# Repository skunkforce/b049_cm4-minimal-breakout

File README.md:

# edgy_board number b078
This design is part of the [edgy board project](https://github.com/skunkforce/edgy_boards).

# getting started
This repository uses submodules. After cloning use the command 

```$ git submodule update --init --recursive```

to pull the submodules before opening the project with kicad. 

# Tests
Tests can be found in TESTS.md

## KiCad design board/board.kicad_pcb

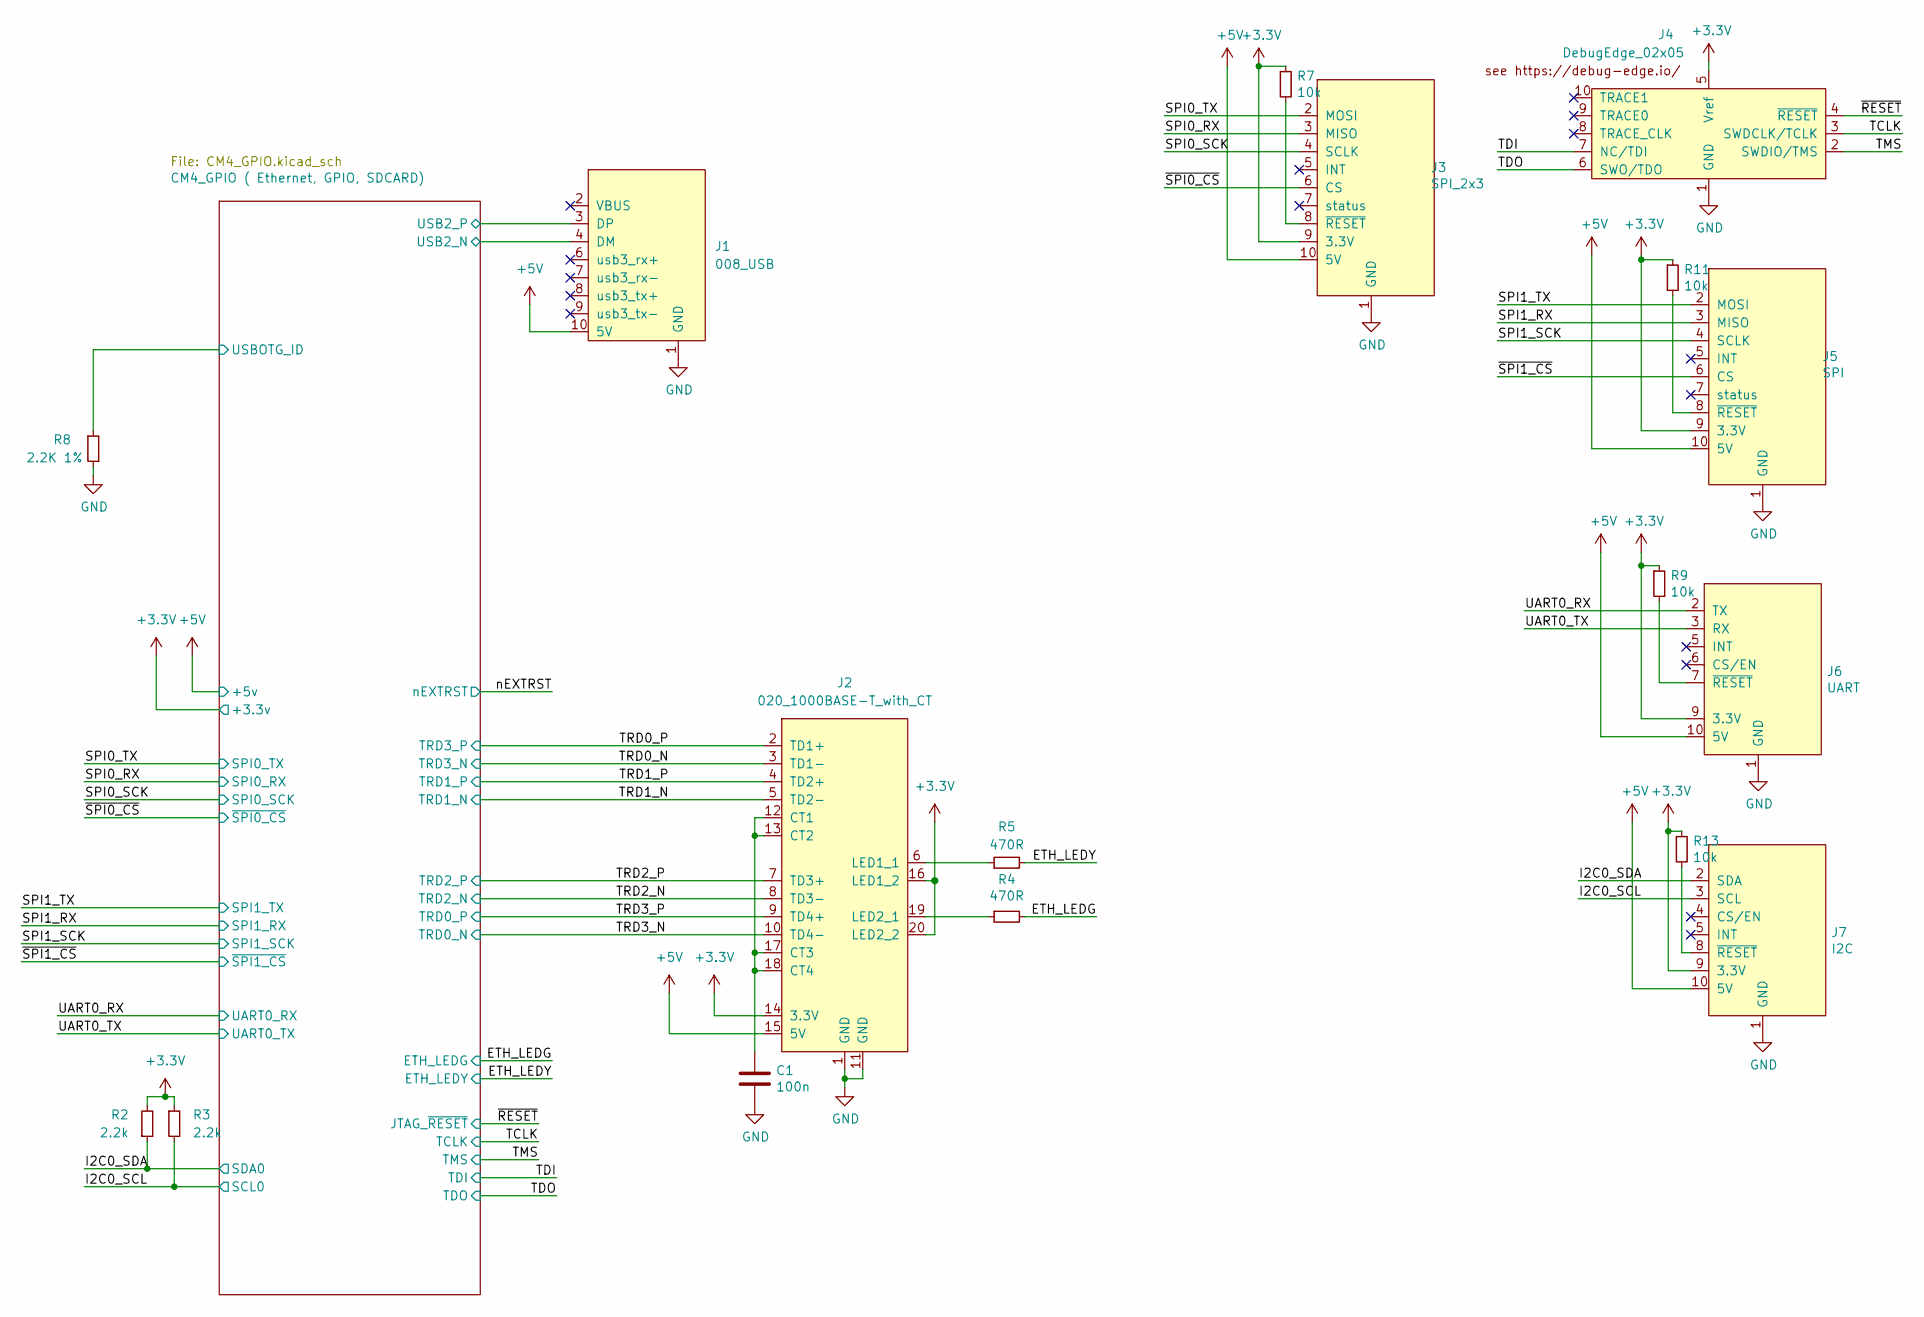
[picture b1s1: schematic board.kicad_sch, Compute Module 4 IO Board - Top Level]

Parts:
C1: 100n; C_0402_1005Metric; Part Description 0.1uF 10% 16V Ceramic Capacitor X7R 040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
J1: 008_USB; on_edge_2x05_host
J2: 020_1000BASE-T_with_CT; on_edge_2x10_host
J3: SPI_2x3; on_edge_2x05_up_host
J4: DebugEdge_02x05; debug_edge_2x05_host
J5: SPI; on_edge_2x05_host
J6: UART; on_edge_2x05_host
J7: I2C; on_edge_2x05_host
R2, R3: 2.2k; R_0603_1608Metric
R4, R5: 470R; R_0402_1005Metric; Part Description Resistor 470R M1005 1% 63mW
R7, R9, R11, R13: 10k; R_0603_1608Metric
R8: 2.2K 1%; R_0402_1005Metric; Part Description Resistor 2.2K M1005 1% 63mW

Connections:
+3.3V: J2.14 (3.3V), J2.16 (LED1_2), J2.20 (LED2_2), J3.9 (3.3V), J4.5 (Vref), J5.9 (3.3V), J6.9 (3.3V), J7.9 (3.3V), R2.2, R3.1, R7.1, R9.1, R11.1, R13.1; also elsewhere on the board
+5V: J1.10 (5V), J2.15 (5V), J3.10 (5V), J5.10 (5V), J6.10 (5V), J7.10 (5V); also elsewhere on the board
/CM4_GPIO ( Ethernet, GPIO, SDCARD)/USB2_N: J1.4 (DM); also elsewhere on the board
/CM4_GPIO ( Ethernet, GPIO, SDCARD)/USB2_P: J1.3 (DP); also elsewhere on the board
/CM4_GPIO ( Ethernet, GPIO, SDCARD)/USBOTG_ID: R8.1; also elsewhere on the board
/ETH_LEDG: R4.2; also elsewhere on the board
/ETH_LEDY: R5.2; also elsewhere on the board
/I2C0_SCL: J7.3 (SCL), R3.2; also elsewhere on the board
/I2C0_SDA: J7.2 (SDA), R2.1; also elsewhere on the board
/SPI0_RX: J3.3 (MISO); also elsewhere on the board
/SPI0_SCK: J3.4 (SCLK); also elsewhere on the board
/SPI0_TX: J3.2 (MOSI); also elsewhere on the board
/SPI1_RX: J5.3 (MISO); also elsewhere on the board
/SPI1_SCK: J5.4 (SCLK); also elsewhere on the board
/SPI1_TX: J5.2 (MOSI); also elsewhere on the board
/TCLK: J4.3 (SWDCLK/TCLK); also elsewhere on the board
/TDI: J4.7 (NC/TDI); also elsewhere on the board
/TDO: J4.6 (SWO/TDO); also elsewhere on the board
/TMS: J4.2 (SWDIO/TMS); also elsewhere on the board
/TRD0_N: J2.3 (TD1-); also elsewhere on the board
/TRD0_P: J2.2 (TD1+); also elsewhere on the board
/TRD1_N: J2.5 (TD2-); also elsewhere on the board
/TRD1_P: J2.4 (TD2+); also elsewhere on the board
/TRD2_N: J2.8 (TD3-); also elsewhere on the board
/TRD2_P: J2.7 (TD3+); also elsewhere on the board
/TRD3_N: J2.10 (TD4-); also elsewhere on the board
/TRD3_P: J2.9 (TD4+); also elsewhere on the board
/UART0_RX: J6.2 (TX); also elsewhere on the board
/UART0_TX: J6.3 (RX); also elsewhere on the board
/~RESET: J4.4 (~RESET); also elsewhere on the board
/~SPI0_CS: J3.6 (CS); also elsewhere on the board
/~SPI1_CS: J5.6 (CS); also elsewhere on the board
GND: C1.2, J1.1 (GND), J2.1 (GND), J2.11 (GND), J3.1 (GND), J4.1 (GND), J5.1 (GND), J6.1 (GND), J7.1 (GND), R8.2; also elsewhere on the board
unnamed: C1.1, J2.12 (CT1), J2.13 (CT2), J2.17 (CT3), J2.18 (CT4)
unnamed: J2.6 (LED1_1), R5.1
unnamed: J2.19 (LED2_1), R4.1
unnamed: J3.8 (~RESET), R7.2
unnamed: J5.8 (~RESET), R11.2
unnamed: J6.7 (~RESET), R9.2
unnamed: J7.8 (~RESET), R13.2

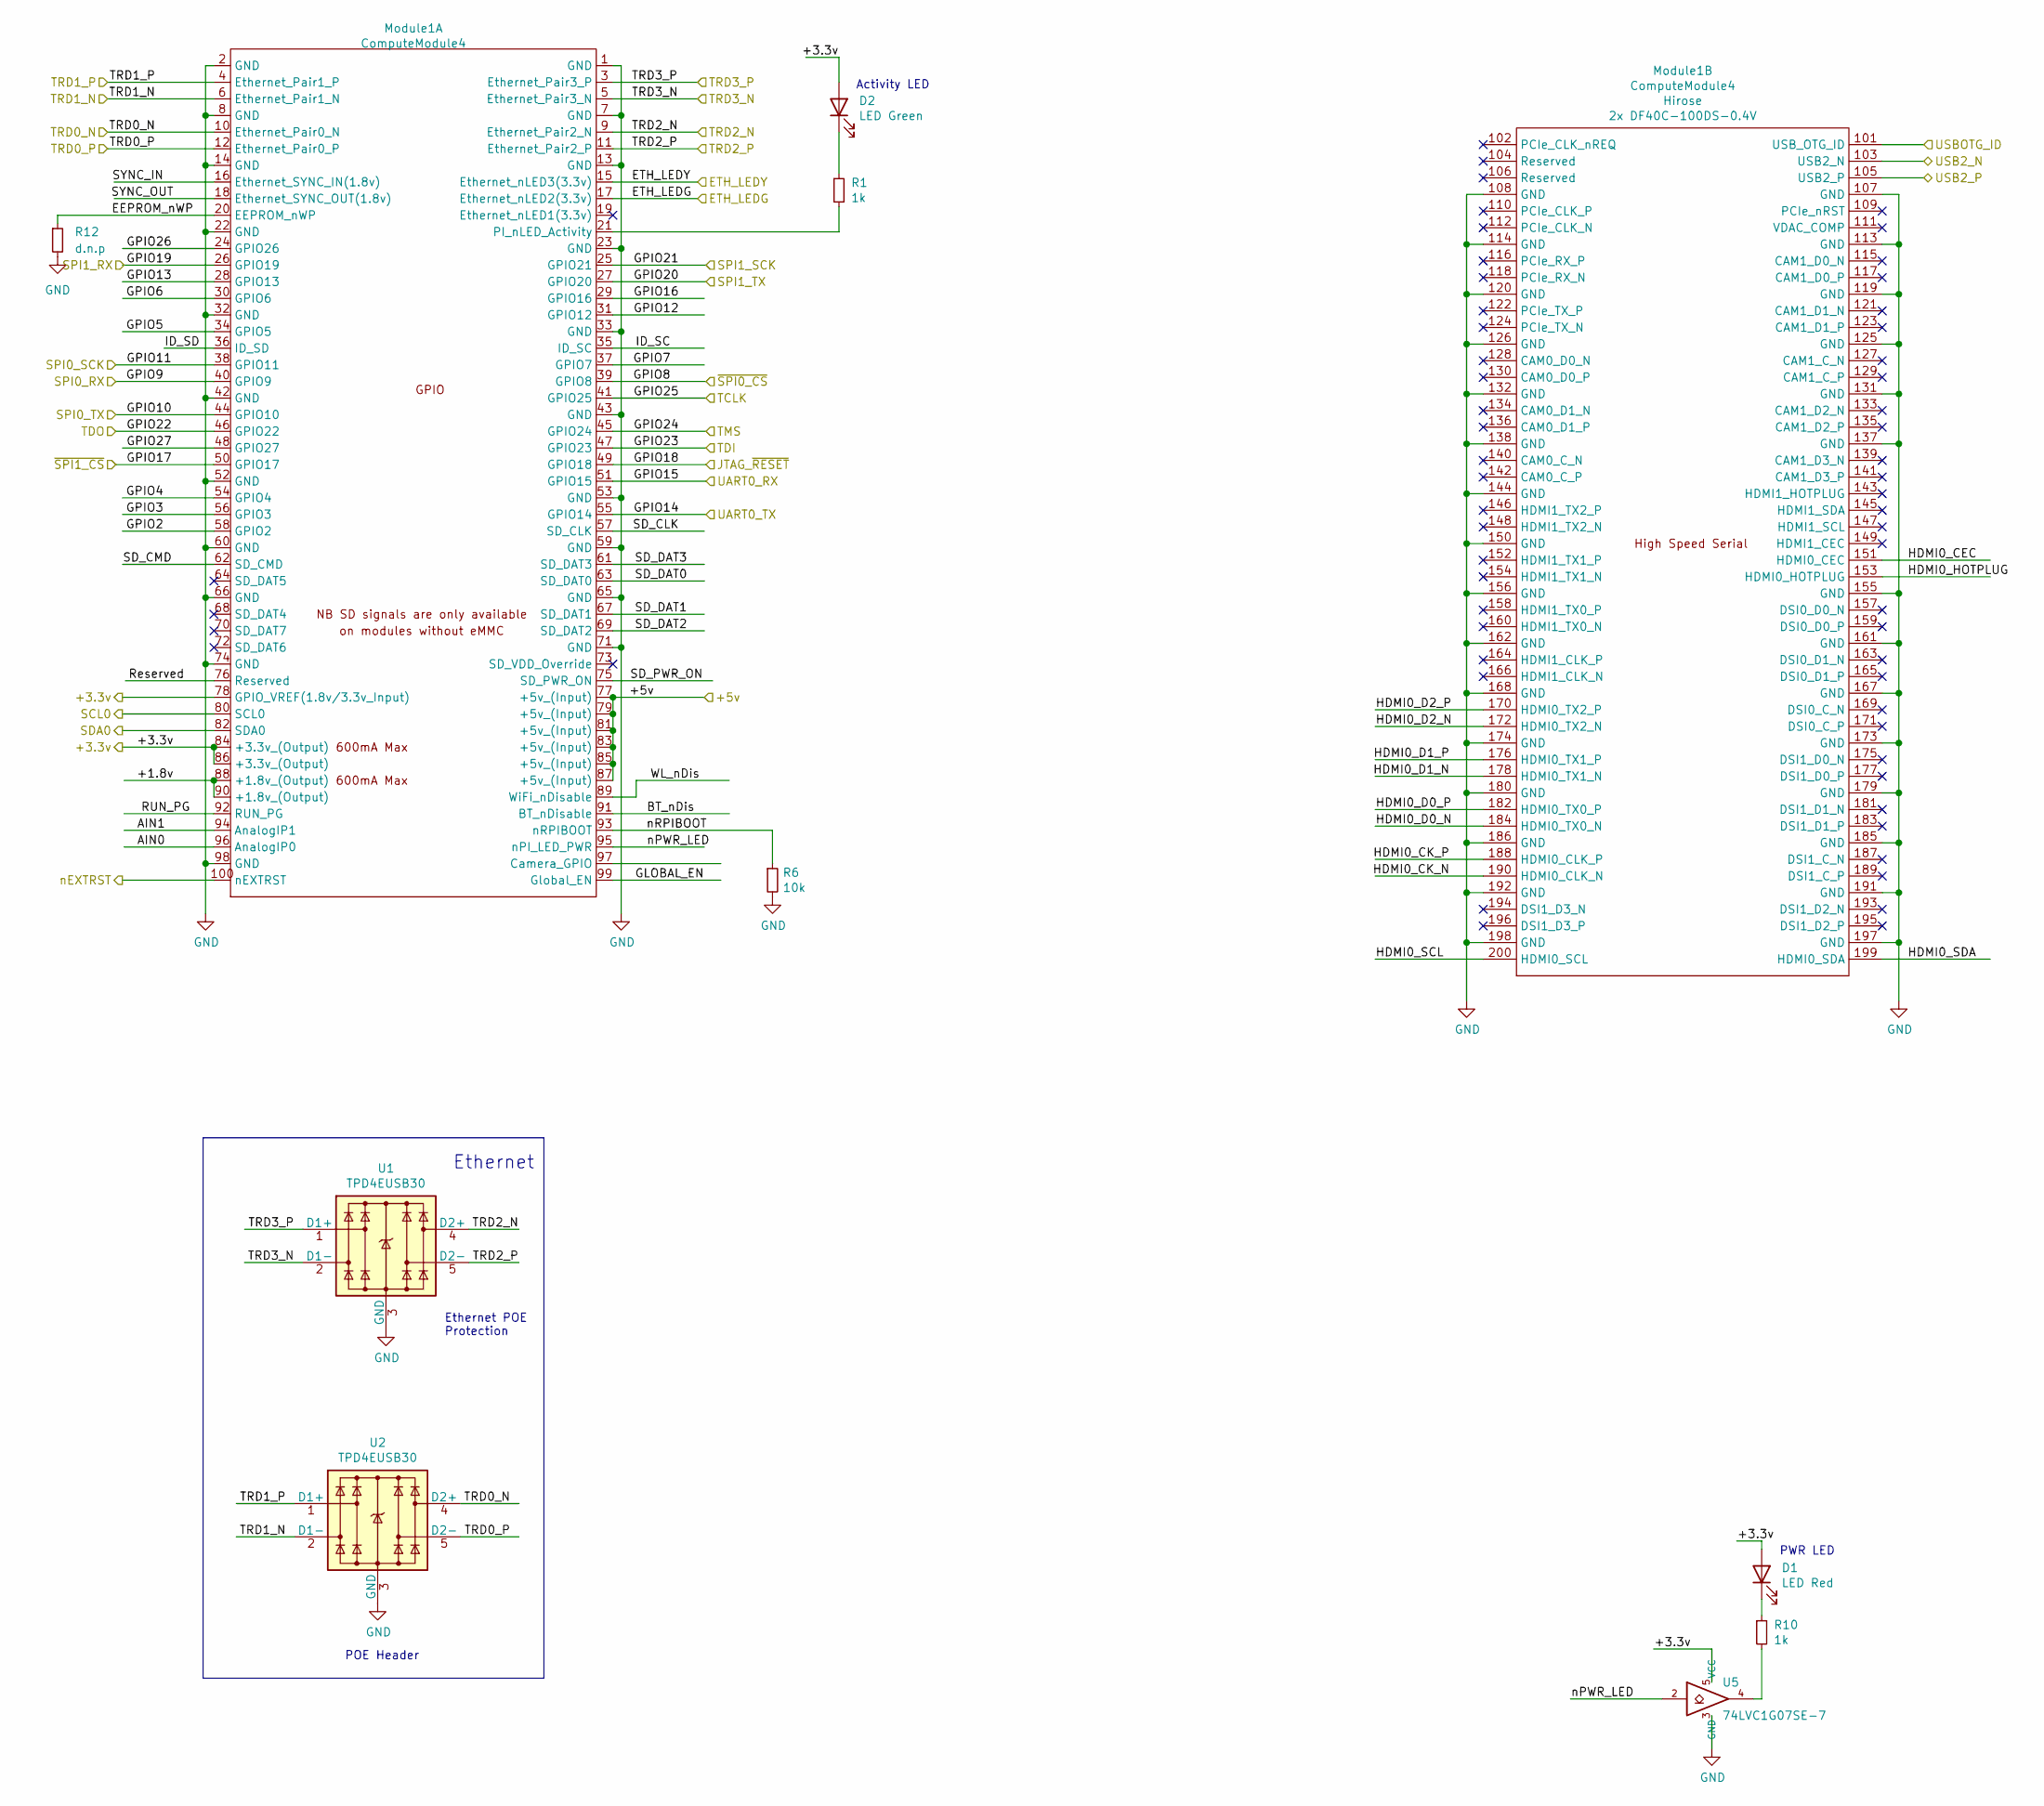
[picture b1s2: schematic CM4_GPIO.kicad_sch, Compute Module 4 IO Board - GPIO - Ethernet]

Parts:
D1: LED Red; LED_0603_1608Metric; Part Description Red 620nm LED Indication - Discrete 2.2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
D2: LED Green; LED_0603_1608Metric; Part Description Green 572nm LED Indication - Discrete 2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
Module1: ComputeModule4; Raspberry-Pi-4-Compute-Module; Part Description 100 Position Connector Receptacle, Cent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
R1, R10: 1k; R_0402_1005Metric; Part Description Resistor 1K M1005 1% 63mW
R6: 10k; R_0603_1608Metric
R12: d.n.p; R_0603_1608Metric
U1, U2: TPD4EUSB30; USON-10_2.5x1.0mm_P0.5mm; Part Description Quad TVS diode for high speed signals (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
U5: 74LVC1G07SE-7; SOT-353_SC-70-5; Part Description Buffer, Non-Inverting 1 Element 1 Bit p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

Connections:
+3.3V: D1.2 (A), D2.2 (A), Module1.78 (GPIO_VREF(1.8v/3.3v_Input)), Module1.84 (+3.3v_(Output)), Module1.86 (+3.3v_(Output)), U5.5 (VCC); also elsewhere on the board
+5V: Module1.77 (+5v_(Input)), Module1.79 (+5v_(Input)), Module1.81 (+5v_(Input)), Module1.83 (+5v_(Input)), Module1.85 (+5v_(Input)), Module1.87 (+5v_(Input)); also elsewhere on the board
/CM4_GPIO ( Ethernet, GPIO, SDCARD)/+1.8v: Module1.88 (+1.8v_(Output)), Module1.90 (+1.8v_(Output))
/CM4_GPIO ( Ethernet, GPIO, SDCARD)/AIN0: Module1.96 (AnalogIP0)
/CM4_GPIO ( Ethernet, GPIO, SDCARD)/AIN1: Module1.94 (AnalogIP1)
/CM4_GPIO ( Ethernet, GPIO, SDCARD)/BT_nDis: Module1.91 (BT_nDisable)
/CM4_GPIO ( Ethernet, GPIO, SDCARD)/EEPROM_nWP: Module1.20 (EEPROM_nWP), R12.1
/CM4_GPIO ( Ethernet, GPIO, SDCARD)/GLOBAL_EN: Module1.99 (Global_EN)
/CM4_GPIO ( Ethernet, GPIO, SDCARD)/GPIO2: Module1.58 (GPIO2)
/CM4_GPIO ( Ethernet, GPIO, SDCARD)/GPIO3: Module1.56 (GPIO3)
/CM4_GPIO ( Ethernet, GPIO, SDCARD)/GPIO4: Module1.54 (GPIO4)
/CM4_GPIO ( Ethernet, GPIO, SDCARD)/GPIO5: Module1.34 (GPIO5)
/CM4_GPIO ( Ethernet, GPIO, SDCARD)/GPIO6: Module1.30 (GPIO6)
/CM4_GPIO ( Ethernet, GPIO, SDCARD)/GPIO7: Module1.37 (GPIO7)
/CM4_GPIO ( Ethernet, GPIO, SDCARD)/GPIO12: Module1.31 (GPIO12)
/CM4_GPIO ( Ethernet, GPIO, SDCARD)/GPIO13: Module1.28 (GPIO13)
/CM4_GPIO ( Ethernet, GPIO, SDCARD)/GPIO16: Module1.29 (GPIO16)
/CM4_GPIO ( Ethernet, GPIO, SDCARD)/GPIO26: Module1.24 (GPIO26)
/CM4_GPIO ( Ethernet, GPIO, SDCARD)/GPIO27: Module1.48 (GPIO27)
/CM4_GPIO ( Ethernet, GPIO, SDCARD)/HDMI0_CEC: Module1.151 (HDMI0_CEC)
/CM4_GPIO ( Ethernet, GPIO, SDCARD)/HDMI0_CK_N: Module1.190 (HDMI0_CLK_N)
/CM4_GPIO ( Ethernet, GPIO, SDCARD)/HDMI0_CK_P: Module1.188 (HDMI0_CLK_P)
/CM4_GPIO ( Ethernet, GPIO, SDCARD)/HDMI0_D0_N: Module1.184 (HDMI0_TX0_N)
/CM4_GPIO ( Ethernet, GPIO, SDCARD)/HDMI0_D0_P: Module1.182 (HDMI0_TX0_P)
/CM4_GPIO ( Ethernet, GPIO, SDCARD)/HDMI0_D1_N: Module1.178 (HDMI0_TX1_N)
/CM4_GPIO ( Ethernet, GPIO, SDCARD)/HDMI0_D1_P: Module1.176 (HDMI0_TX1_P)
/CM4_GPIO ( Ethernet, GPIO, SDCARD)/HDMI0_D2_N: Module1.172 (HDMI0_TX2_N)
/CM4_GPIO ( Ethernet, GPIO, SDCARD)/HDMI0_D2_P: Module1.170 (HDMI0_TX2_P)
/CM4_GPIO ( Ethernet, GPIO, SDCARD)/HDMI0_HOTPLUG: Module1.153 (HDMI0_HOTPLUG)
/CM4_GPIO ( Ethernet, GPIO, SDCARD)/HDMI0_SCL: Module1.200 (HDMI0_SCL)
/CM4_GPIO ( Ethernet, GPIO, SDCARD)/HDMI0_SDA: Module1.199 (HDMI0_SDA)
/CM4_GPIO ( Ethernet, GPIO, SDCARD)/ID_SC: Module1.35 (ID_SC)
/CM4_GPIO ( Ethernet, GPIO, SDCARD)/ID_SD: Module1.36 (ID_SD)
/CM4_GPIO ( Ethernet, GPIO, SDCARD)/RUN_PG: Module1.92 (RUN_PG)
/CM4_GPIO ( Ethernet, GPIO, SDCARD)/Reserved: Module1.76 (Reserved)
/CM4_GPIO ( Ethernet, GPIO, SDCARD)/SD_CLK: Module1.57 (SD_CLK)
/CM4_GPIO ( Ethernet, GPIO, SDCARD)/SD_CMD: Module1.62 (SD_CMD)
/CM4_GPIO ( Ethernet, GPIO, SDCARD)/SD_DAT0: Module1.63 (SD_DAT0)
/CM4_GPIO ( Ethernet, GPIO, SDCARD)/SD_DAT1: Module1.67 (SD_DAT1)
/CM4_GPIO ( Ethernet, GPIO, SDCARD)/SD_DAT2: Module1.69 (SD_DAT2)
/CM4_GPIO ( Ethernet, GPIO, SDCARD)/SD_DAT3: Module1.61 (SD_DAT3)
/CM4_GPIO ( Ethernet, GPIO, SDCARD)/SD_PWR_ON: Module1.75 (SD_PWR_ON)
/CM4_GPIO ( Ethernet, GPIO, SDCARD)/SYNC_IN: Module1.16 (Ethernet_SYNC_IN(1.8v))
/CM4_GPIO ( Ethernet, GPIO, SDCARD)/SYNC_OUT: Module1.18 (Ethernet_SYNC_OUT(1.8v))
/CM4_GPIO ( Ethernet, GPIO, SDCARD)/USB2_N: Module1.103 (USB2_N); also elsewhere on the board
/CM4_GPIO ( Ethernet, GPIO, SDCARD)/USB2_P: Module1.105 (USB2_P); also elsewhere on the board
/CM4_GPIO ( Ethernet, GPIO, SDCARD)/USBOTG_ID: Module1.101 (USB_OTG_ID); also elsewhere on the board
/CM4_GPIO ( Ethernet, GPIO, SDCARD)/WL_nDis: Module1.89 (WiFi_nDisable)
/CM4_GPIO ( Ethernet, GPIO, SDCARD)/nPWR_LED: Module1.95 (nPI_LED_PWR), U5.2
/CM4_GPIO ( Ethernet, GPIO, SDCARD)/nRPIBOOT: Module1.93 (nRPIBOOT), R6.1
/ETH_LEDG: Module1.17 (Ethernet_nLED2(3.3v)); also elsewhere on the board
/ETH_LEDY: Module1.15 (Ethernet_nLED3(3.3v)); also elsewhere on the board
/I2C0_SCL: Module1.80 (SCL0); also elsewhere on the board
/I2C0_SDA: Module1.82 (SDA0); also elsewhere on the board
/SPI0_RX: Module1.40 (GPIO9); also elsewhere on the board
/SPI0_SCK: Module1.38 (GPIO11); also elsewhere on the board
/SPI0_TX: Module1.44 (GPIO10); also elsewhere on the board
/SPI1_RX: Module1.26 (GPIO19); also elsewhere on the board
/SPI1_SCK: Module1.25 (GPIO21); also elsewhere on the board
/SPI1_TX: Module1.27 (GPIO20); also elsewhere on the board
/TCLK: Module1.41 (GPIO25); also elsewhere on the board
/TDI: Module1.47 (GPIO23); also elsewhere on the board
/TDO: Module1.46 (GPIO22); also elsewhere on the board
/TMS: Module1.45 (GPIO24); also elsewhere on the board
/TRD0_N: Module1.5 (Ethernet_Pair3_N), U1.2 (D1-), U1.9; also elsewhere on the board
/TRD0_P: Module1.3 (Ethernet_Pair3_P), U1.1 (D1+), U1.10; also elsewhere on the board
/TRD1_N: Module1.6 (Ethernet_Pair1_N), U2.2 (D1-), U2.9; also elsewhere on the board
/TRD1_P: Module1.4 (Ethernet_Pair1_P), U2.1 (D1+), U2.10; also elsewhere on the board
/TRD2_N: Module1.9 (Ethernet_Pair2_N), U1.4 (D2+), U1.7; also elsewhere on the board
/TRD2_P: Module1.11 (Ethernet_Pair2_P), U1.5 (D2-), U1.6; also elsewhere on the board
/TRD3_N: Module1.10 (Ethernet_Pair0_N), U2.4 (D2+), U2.7; also elsewhere on the board
/TRD3_P: Module1.12 (Ethernet_Pair0_P), U2.5 (D2-), U2.6; also elsewhere on the board
/UART0_RX: Module1.51 (GPIO15); also elsewhere on the board
/UART0_TX: Module1.55 (GPIO14); also elsewhere on the board
/nEXTRST: Module1.100 (nEXTRST)
/~RESET: Module1.49 (GPIO18); also elsewhere on the board
/~SPI0_CS: Module1.39 (GPIO8); also elsewhere on the board
/~SPI1_CS: Module1.50 (GPIO17); also elsewhere on the board
GND: Module1.1 (GND), Module1.2 (GND), Module1.7 (GND), Module1.8 (GND), Module1.13 (GND), Module1.14 (GND), Module1.22 (GND), Module1.23 (GND), Module1.32 (GND), Module1.33 (GND), Module1.42 (GND), Module1.43 (GND), Module1.52 (GND), Module1.53 (GND), Module1.59 (GND), Module1.60 (GND), Module1.65 (GND), Module1.66 (GND), Module1.71 (GND), Module1.74 (GND), Module1.98 (GND), Module1.107 (GND), Module1.108 (GND), Module1.113 (GND), Module1.114 (GND), Module1.119 (GND), Module1.120 (GND), Module1.125 (GND), Module1.126 (GND), Module1.131 (GND), Module1.132 (GND), Module1.137 (GND), Module1.138 (GND), Module1.144 (GND), Module1.150 (GND), Module1.155 (GND), Module1.156 (GND), Module1.161 (GND), Module1.162 (GND), Module1.167 (GND), Module1.168 (GND), Module1.173 (GND), Module1.174 (GND), Module1.179 (GND), Module1.180 (GND), Module1.185 (GND), Module1.186 (GND), Module1.191 (GND), Module1.192 (GND), Module1.197 (GND), Module1.198 (GND), R6.2, R12.2, U1.3 (GND), U1.8 (GND), U2.3 (GND), U2.8 (GND), U5.3 (GND); also elsewhere on the board
unnamed: D1.1 (K), R10.1
unnamed: D2.1 (K), R1.1
unnamed: Module1.21 (PI_nLED_Activity), R1.2
unnamed: R10.2, U5.4

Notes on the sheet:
PWR LED
Ethernet POE Protection
Ethernet
Activity LED
POE Header

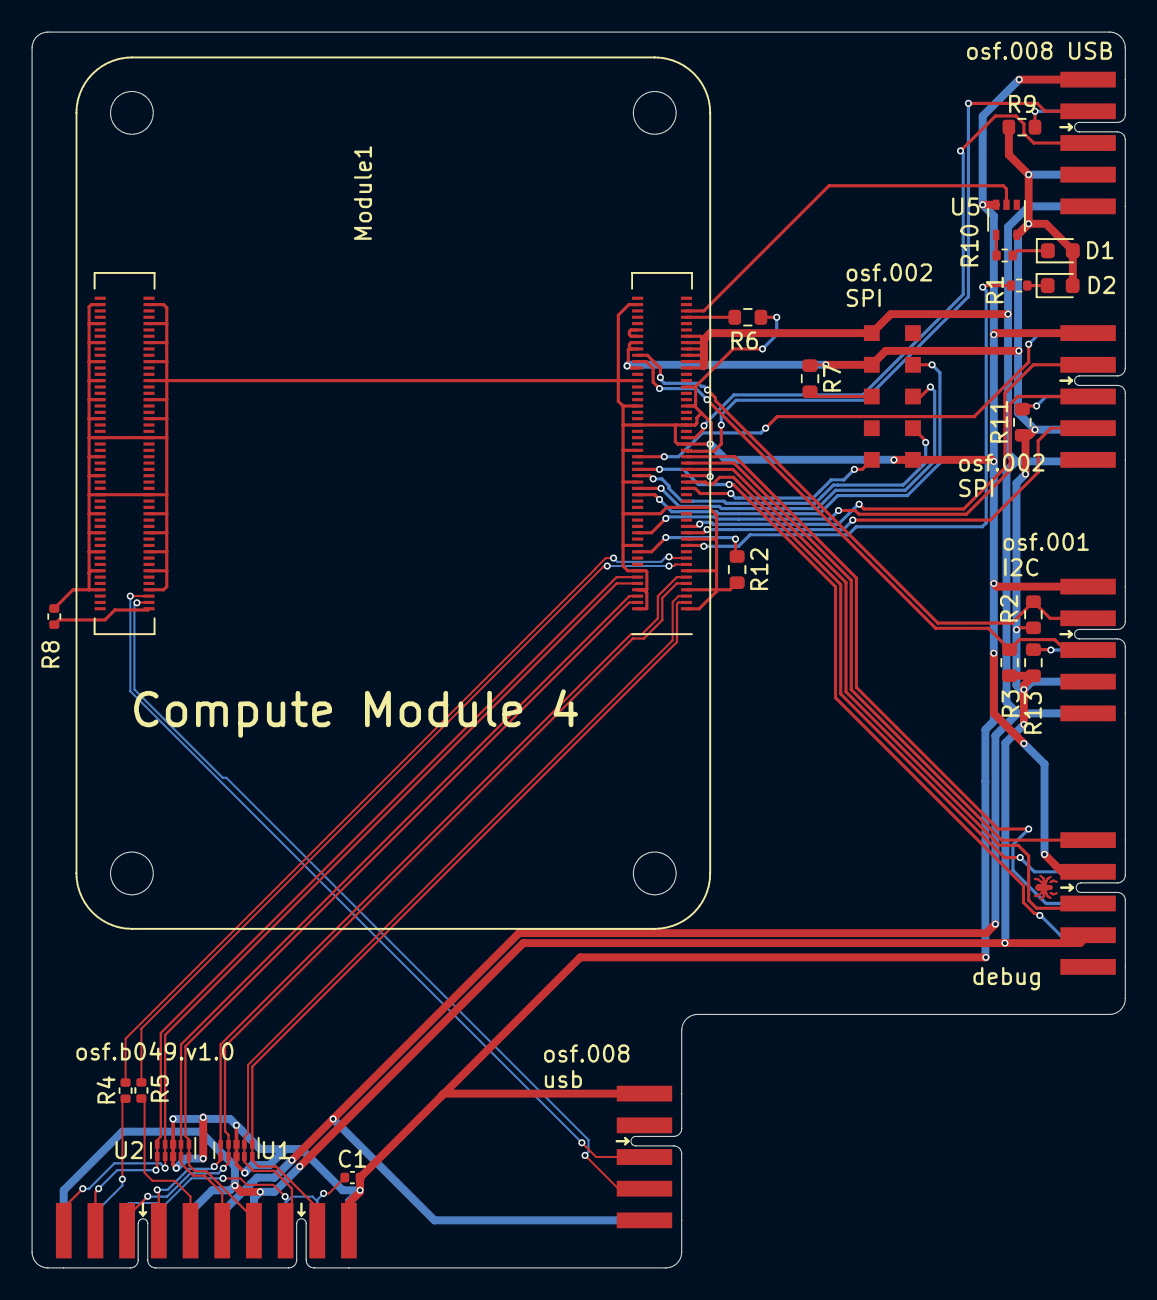
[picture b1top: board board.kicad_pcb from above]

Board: 4 copper layers, 69.0 x 78.0 mm, 27 parts (0 on the bottom side), 48 nets.

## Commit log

2023-11-18 initial
2023-11-18 fineished routing

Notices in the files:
board/CM4_GPIO.kicad_sch:
© 2020-2022 Raspberry Pi Ltd (formerly Raspberry Pi (Trading) Ltd.)
